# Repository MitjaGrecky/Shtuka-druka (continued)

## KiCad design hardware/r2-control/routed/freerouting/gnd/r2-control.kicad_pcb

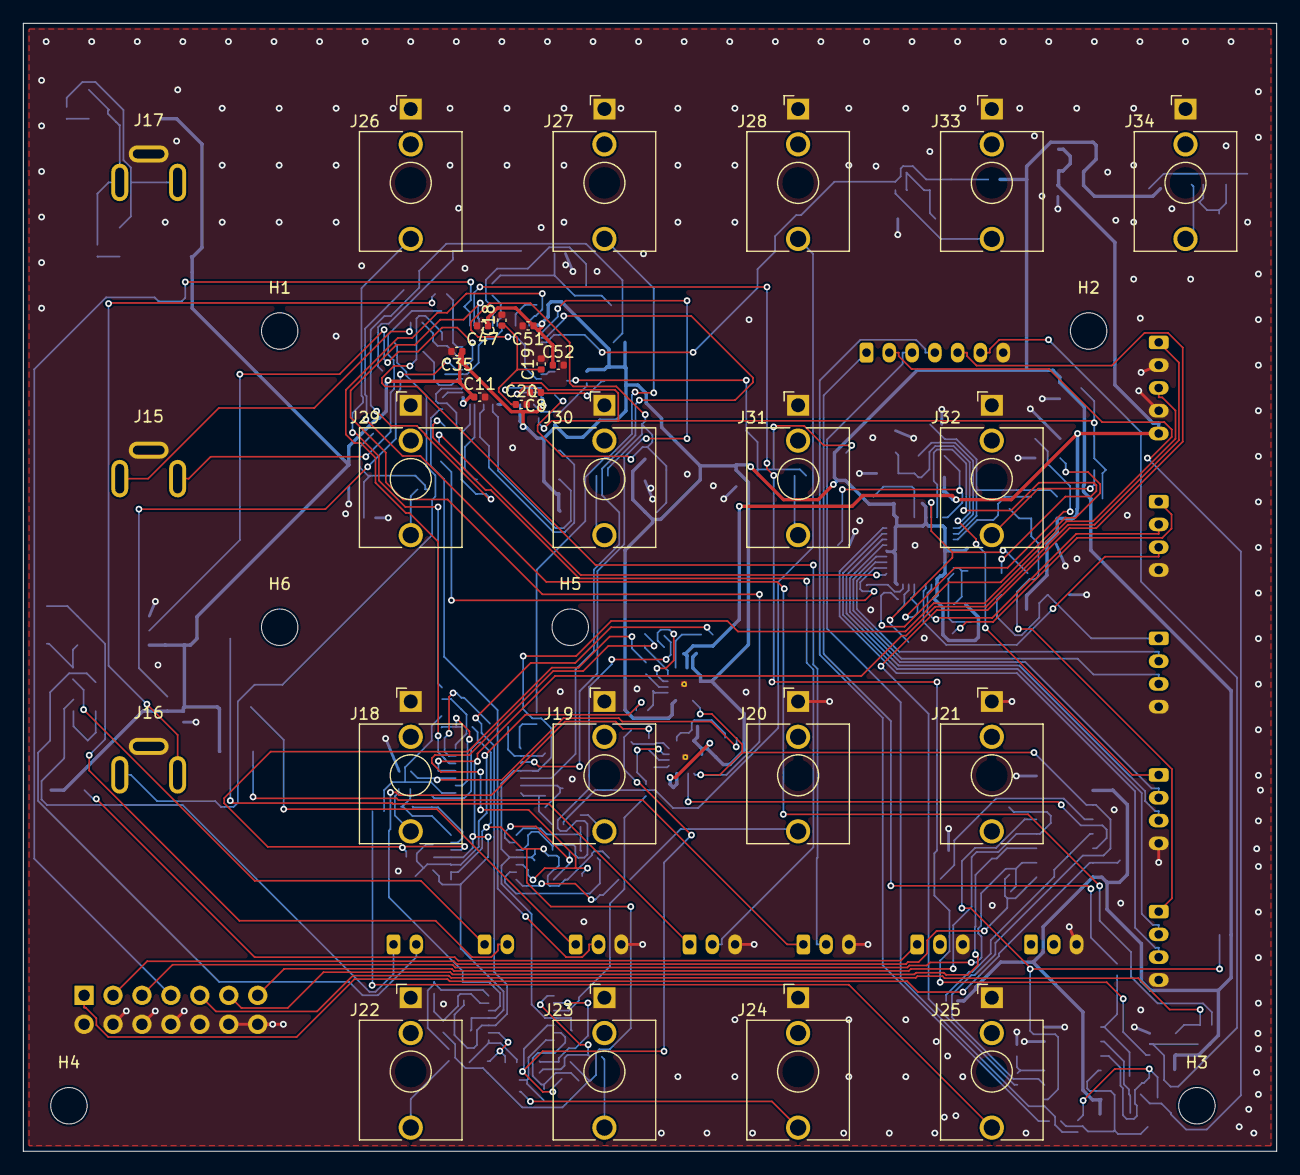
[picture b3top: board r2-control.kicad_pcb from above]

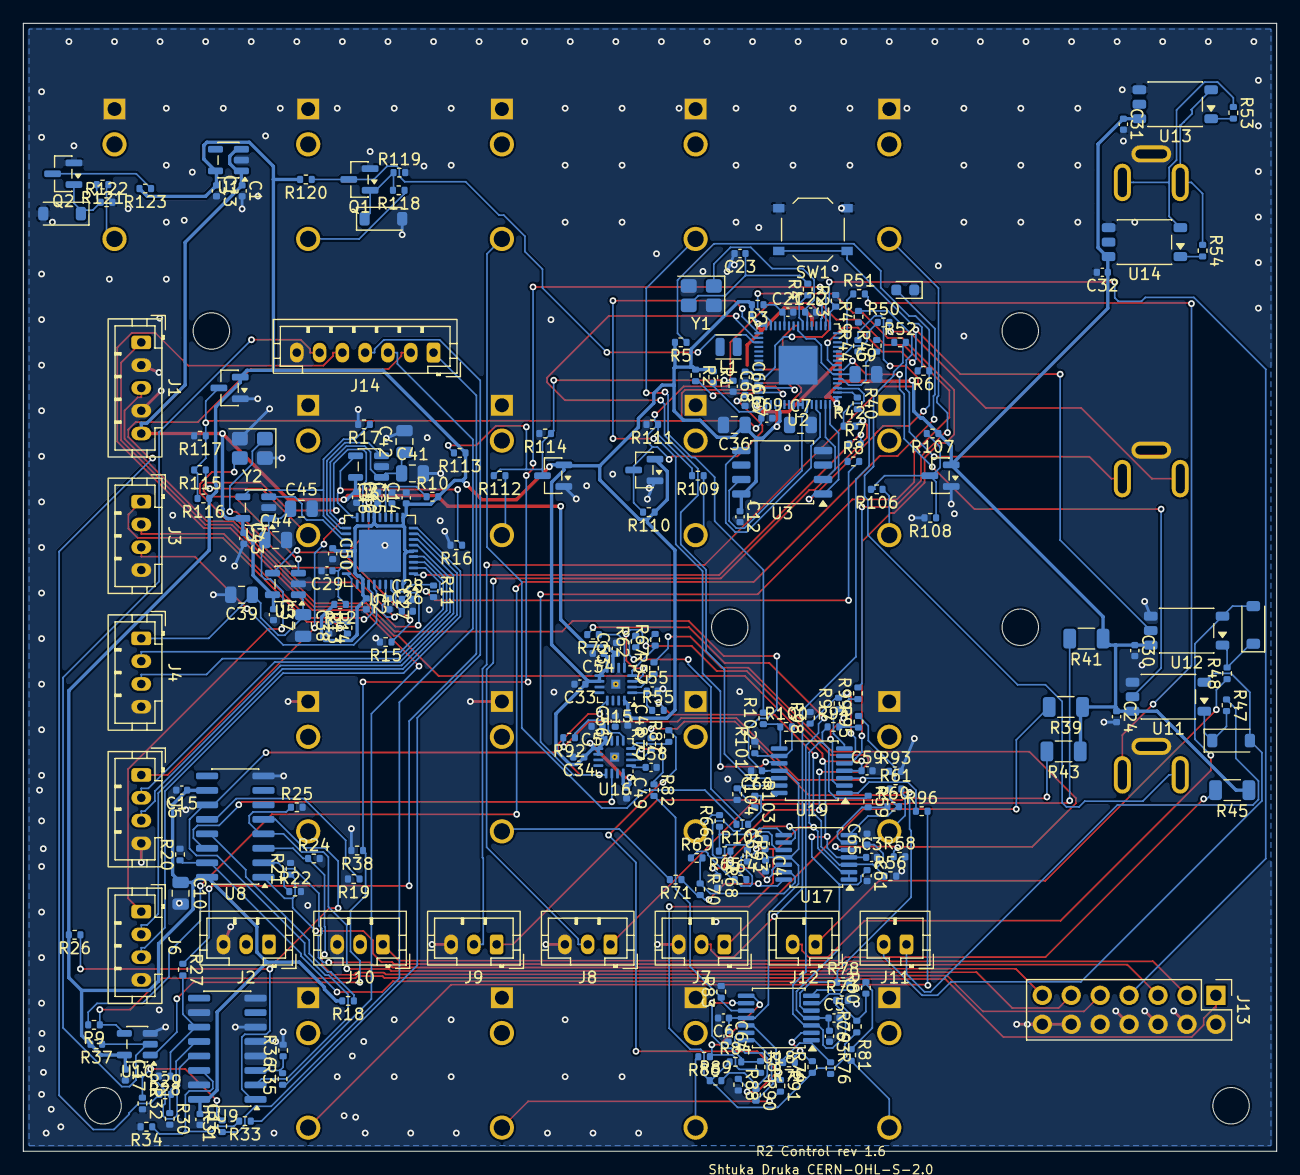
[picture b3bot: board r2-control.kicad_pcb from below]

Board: 4 copper layers, 110.0 x 99.0 mm, 266 parts (231 on the bottom side), 184 nets.

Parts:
C1, C2, C8, C29: 1u; C_0402_1005Metric
C3, C4, C5, C6, C11, C12, C13, C14, C15, C16, C17, C18, C19, C20, C21, C24, C25, C26, C30, C31, C32, C33, C34, C35, C37, C40, C43, C46, C47, C48, C49, C50, C51, C52, C53, C54, C56, C57, C59, C60, C61, C62, C63, C64, C65: 100n; C_0402_1005Metric
C7, C9, C10, C36: 4.7u; C_0805_2012Metric
C22, C23: 15p; C_0402_1005Metric
C27, C28: 18p; C_0402_1005Metric
C38, C39, C41, C42, C44, C45: 22u 10V; C_0805_2012Metric
C55, C58: 220n; C_0402_1005Metric
C66, C67, C68, C69: 10n; C_0402_1005Metric
D1: green; LED_0603_1608Metric
D2, D3, D8, D9: 1N4148W; D_SOD-123
D4, D5, D6, D7: BAT54S; SOT-23
H1, H2, H3, H4, H5, H6: M3; MountingHole_3.2mm_M3_ISO7380
J1: Power from PW; JST_PH_B5B-PH-K_1x05_P2.00mm_Vertical
J2: SWD; JST_PH_B3B-PH-K_1x03_P2.00mm_Vertical
J3: USB up; JST_PH_B4B-PH-K_1x04_P2.00mm_Vertical
J4, J5, J6: USB down; JST_PH_B4B-PH-K_1x04_P2.00mm_Vertical
J7: DIN OUT 1; JST_PH_B3B-PH-K_1x03_P2.00mm_Vertical
J8: DIN OUT 2; JST_PH_B3B-PH-K_1x03_P2.00mm_Vertical
J9: DIN OUT 3; JST_PH_B3B-PH-K_1x03_P2.00mm_Vertical
J10: DIN OUT 4; JST_PH_B3B-PH-K_1x03_P2.00mm_Vertical
J11: DIN IN 1; JST_PH_B2B-PH-K_1x02_P2.00mm_Vertical
J12: DIN IN 2; JST_PH_B2B-PH-K_1x02_P2.00mm_Vertical
J13: to A1/R1; PinHeader_2x07_P2.54mm_Vertical
J14: detect and alert; JST_PH_B7B-PH-K_1x07_P2.00mm_Vertical
J15, J16, J17: PJ-3920-3A; Jack_3.5mm_Hroparts_PJ-3920-3A_Vertical
J18, J19, J20, J21, J22, J23, J24, J25, J26, J27, J28, J29, J30, J31, J32, J33, J34: PJ398SM; Jack_3.5mm_QingPu_WQP-PJ398SM_Vertical_CircularHoles
L1: 3.3uH; L_Abracon_AOTA-B201610S
Q1, Q2: MMBT3904; SOT-23
R1, R2: 33; R_0402_1005Metric
R3, R5, R10, R12, R18, R26, R27, R29, R31, R33, R35, R37, R55, R56, R57, R59, R62, R64, R67, R69, R72, R74, R77, R79, R82, R84, R87, R89, R92, R94, R98, R101, R104, R120, R123: 10k; R_0402_1005Metric
R4, R6, R9, R61, R66, R71, R76, R81, R86, R91, R96, R99, R102, R105: 1k; R_0402_1005Metric
R7, R8: 27; R_0402_1005Metric
R11: 12k; R_0402_1005Metric
R13, R14, R15, R16, R17, R19, R20, R21, R22, R23, R24, R25, R38, R106, R109, R112, R115, R119, R122: 100k; R_0402_1005Metric
R28, R30, R32, R34, R36: 220k; R_0402_1005Metric
R39, R41, R43, R45: 33; R_1206_3216Metric
R40, R42, R44, R46: 10; R_0402_1005Metric
R47, R48, R53, R54: 220; R_0402_1005Metric
R49, R50, R51, R52: 22; R_0402_1005Metric
R58, R60, R63, R65, R68, R70, R73, R75, R78, R80, R83, R85, R88, R90, R93, R95: 80.6k; R_0402_1005Metric
R97, R100, R103: 5.1k; R_0402_1005Metric
R107, R110, R113, R116: 33k; R_0402_1005Metric
R108, R111, R114, R117: 39k; R_0402_1005Metric
R118, R121: 22k; R_0402_1005Metric
SW1: BOOTSEL; SW_Push_1P1T_XKB_TS-1187A
U1: AP2112K-3.3; SOT-23-5
U2: RP2350A; QFN-60-1EP_7x7mm_P0.4mm_EP3.4x3.4mm
U3: W25Q128JVSIQ; SOIC-8_5.3x5.3mm_P1.27mm
U4: USB2514B; QFN-36-1EP_6x6mm_P0.5mm_EP3.7x3.7mm
U5, U6, U7: TPS2051B; SOT-23-5
U8: 74HC595; SOIC-16_3.9x9.9mm_P1.27mm
U9: 74HC165; SOIC-16_3.9x9.9mm_P1.27mm
U10: 74LVC1G08; SOT-23-5
U11, U12, U13, U14: TLP2361; SO-5-6_4.55x3.7mm_P1.27mm
U15, U16: DAC80504; Texas_RTE0016D_WQFN-16-1EP_3x3mm_P0.5mm_EP0.8x0.8mm_Thermal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
U17, U18, U19: OPA4197; TSSOP-14_4.4x5mm_P0.65mm
Y1: 12MHz; Crystal_SMD_3225-4Pin_3.2x2.5mm
Y2: 24MHz; Crystal_SMD_3225-4Pin_3.2x2.5mm

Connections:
+3V3: C2.1, C10.1, C11.1, C12.1, C13.1, C14.1, C15.1, C16.1, C17.1, C24.1, C30.1, C31.1, C32.1, C33.1, C34.1, C35.1, C36.1, C46.1, C47.1, C48.1, C49.1, C50.1, C51.1, C52.1, C54.1, C57.1, D4.2, D5.2, D6.2, D7.2, R1.1, R2.1, R3.2, R5.2, R10.2, R12.2, R18.2, R26.2, R37.2, R39.1, R41.1, R43.1, R45.1, R107.1, R110.1, R113.1, R116.1, R120.2, R123.2, U1.5, U2.1, U2.11, U2.20, U2.30, U2.38, U2.45, U2.49, U2.53, U2.54, U3.8, U4.5, U4.10, U4.15, U4.23, U4.29, U4.36, U8.10, U8.16, U9.16, U10.5, U11.6, U12.6, U13.6, U14.6, U15.8, U15.9, U15.10, U15.16, U16.8, U16.9, U16.10, U16.16
+5V: C1.1, C37.1, C40.1, C43.1, C53.1, C56.1, J1.5, U1.1, U1.3, U5.5, U6.5, U7.5, U15.7, U16.7
/+12V: C3.1, C5.1, C59.1, C61.1, C63.1, J1.1, U17.4, U18.4, U19.4
/-12V: C4.1, C6.1, C60.1, C62.1, C64.1, J1.3, U17.11, U18.11, U19.11
/A1_DM: J5.2, U4.6
/A1_DP: J5.3, U4.7
/A1_OC: U4.19, U6.3
/A1_PWR: R16.1, U4.18, U6.4
/A1_VBUS: C41.1, C42.1, J5.1, U6.1
/ADC_AVDD: C8.1, R2.2, U2.44
/ATT1: J13.11, R24.1, U8.3
/ATT2: J13.13, R25.1, U8.4
/BOOTSEL: R6.2, SW1.1
/CLK_IN: Q1.3, R120.1, U2.33
/CLK_IN_B: D8.1, Q1.1, R118.2, R119.1
/CLK_IN_J: J33.T, R118.1
/CLK_OUT1: U2.29, U19.5
/CLK_OUT2: U2.31, U19.10
/CV1_J: J18.T, R61.2
/CV2_J: J19.T, R66.2
/CV3_J: J20.T, R71.2
/CV4_J: J21.T, R76.2
/CV5_J: J22.T, R81.2
/CV6_J: J23.T, R86.2
/CV7_J: J24.T, R91.2
/CV8_J: J25.T, R96.2
/CVI1_J: J29.T, R106.1
/CVI2_J: J30.T, R109.1
/CVI3_J: J31.T, R112.1
/CVI4_J: J32.T, R115.1
/CVIN1: C66.1, D4.3, R106.2, R107.2, R108.1, U2.40
/CVIN2: C67.1, D5.3, R109.2, R110.2, R111.1, U2.41
/CVIN3: C68.1, D6.3, R112.2, R113.2, R114.1, U2.42
/CVIN4: C69.1, D7.3, R115.2, R116.2, R117.1, U2.43
/CVN1: R59.2, R60.1, U17.6
/CVN2: R64.2, R65.1, U17.9
/CVN3: R69.2, R70.1, U17.13
/CVN4: R74.2, R75.1, U18.2
/CVN5: R79.2, R80.1, U18.6
/CVN6: R84.2, R85.1, U18.9
/CVN7: R89.2, R90.1, U18.13
/CVN8: R94.2, R95.1, U19.2
/CVO1: R60.2, R61.1, U17.7
/CVO2: R65.2, R66.1, U17.8
/CVO3: R70.2, R71.1, U17.14
/CVO4: R75.2, R76.1, U18.1
/CVO5: R80.2, R81.1, U18.7
/CVO6: R85.2, R86.1, U18.8
/CVO7: R90.2, R91.1, U18.14
/CVO8: R95.2, R96.1, U19.1
/CVP1: R57.2, R58.1, U17.5
/CVP2: R62.2, R63.1, U17.10
/CVP3: R67.2, R68.1, U17.12
/CVP4: R72.2, R73.1, U18.3
/CVP5: R77.2, R78.1, U18.5
/CVP6: R82.2, R83.1, U18.10
/CVP7: R87.2, R88.1, U18.12
/CVP8: R92.2, R93.1, U19.3
/DAC1: R57.1, U15.2
/DAC2: R62.1, U15.3
/DAC3: R67.1, U15.4
/DAC4: R72.1, U15.5
/DAC5: R77.1, U16.2
/DAC6: R82.1, U16.3
/DAC7: R87.1, U16.4
/DAC8: R92.1, U16.5
/DAC_CS1: U2.27, U15.12
/DAC_CS2: U2.28, U16.12
/DAC_REF1: C55.1, R55.1, U15.1
/DAC_REF2: C58.1, U16.1
/DAC_SCK: U2.18, U8.11, U9.2, U15.13, U16.13
/DAC_SDI: U2.19, U8.14, U15.14, U16.14
/DETI_AUX: R29.2, R30.1, U9.12
/DETI_HP1: R33.2, R34.1, U9.14
/DETI_HP2: R35.2, R36.1, U9.3
/DETI_MAIN: R27.2, R28.1, U9.11
/DETI_RCA: R31.2, R32.1, U9.13
/DET_AUX: J14.2, R29.1
/DET_HP1: J14.4, R33.1
/DET_HP2: J14.5, R35.1
/DET_MAIN: J14.1, R27.1
/DET_PL: R26.1, U8.5, U9.1
/DET_RCA: J14.3, R31.1
/DET_SDO: U2.37, U9.9
/DVDD: C9.1, C18.1, C19.1, C20.1, L1.2, U2.6, U2.23, U2.39, U2.50
/HUB_CRFILT: C25.1, U4.14
/HUB_OCS: R10.1, U4.13
/HUB_PLLFILT: C26.1, U4.34
/HUB_RBIAS: R11.1, U4.35
/HUB_RESET: C29.1, R12.1, U4.26
/HUB_VBUSDET: R13.2, R14.1, U4.27
/HUB_XI: C27.1, U4.33, Y2.1
/HUB_XO: C28.1, U4.32, Y2.3
/LED_K: D1.2, R9.2
/MCU_DM: R7.2, U4.1
/MCU_DM_R: R7.1, U2.51
/MCU_DP: R8.2, U4.2
/MCU_DP_R: R8.1, U2.52
/MI1_4: J11.1, R47.1
/MI1_5: D2.2, J11.2, U11.3
/MI1_A: D2.1, R47.2, U11.1
/MI2_4: J12.1, R48.1
/MI2_5: D3.2, J12.2, U12.3
/MI2_A: D3.1, R48.2, U12.1
/MIDI_RX1: U2.7, U11.5
/MIDI_RX2: U2.8, U12.5
/MIDI_TX1: R40.1, U2.2
/MIDI_TX2: R42.1, U2.3
/MIDI_TX3: R44.1, U2.4
/MIDI_TX4: R46.1, U2.5
/MO1_4: J7.1, R39.2
/MO1_5: J7.2, R40.2
/MO2_4: J8.1, R41.2
/MO2_5: J8.2, R42.2
/MO3_4: J9.1, R43.2
/MO3_5: J9.2, R44.2
/MO4_4: J10.1, R45.2
/MO4_5: J10.2, R46.2
/MUTE: J13.7, R23.1, U2.16
/P2_DM: J4.2, U4.3
/P2_DP: J4.3, U4.4
/P2_OC: U4.17, U5.3
/P2_PWR: R15.1, U4.16, U5.4
/P2_VBUS: C38.1, C39.1, J4.1, U5.1
/PH48_1: J13.1, R20.1, U8.15
/PH48_2: J13.3, R21.1, U8.1
/PHONO: J13.5, R22.1, U8.2
/PM_ALERT: J14.6, R37.1, U10.2
/QSPI_SCLK: U2.56, U3.6
/QSPI_SD0: U2.57, U3.5
/QSPI_SD1: U2.59, U3.2
/QSPI_SD2: U2.58, U3.3
/QSPI_SD3: U2.55, U3.7
/QSPI_SS: R5.1, R6.1, U2.60, U3.1
/R2_OK: J13.9, R9.1, U10.4
/R2_OK_FW: R38.1, U2.17, U10.1
/REFBUF: R59.1, R64.1, R69.1, R74.1, R79.1, R84.1, R89.1, R94.1, U17.1, U17.2
/REFHALF: C65.1, R55.2, R56.1, U17.3
/RST_IN: Q2.3, R123.1, U2.34
/RST_IN_B: D9.1, Q2.1, R121.2, R122.1
/RST_IN_J: J34.T, R121.1
/RST_OUT: U2.32, U19.12
/RUN: C21.1, R3.1, U2.26
/SO1_J: J26.T, R99.2
/SO1_N: R97.2, R98.1, U19.6
/SO1_O: R97.1, R99.1, U19.7
/SO2_J: J27.T, R102.2
/SO2_N: R100.2, R101.1, U19.9
/SO2_O: R100.1, R102.1, U19.8
/SO3_J: J28.T, R105.2
/SO3_N: R103.2, R104.1, U19.13
/SO3_O: R103.1, R105.1, U19.14
/SP_DM: J6.2, U4.8
/SP_DP: J6.3, U4.9
/SP_OC: U4.21, U7.3
/SP_PWR: R17.1, U4.20, U7.4
/SP_VBUS: C44.1, C45.1, J6.1, U7.1
/SWCLK: J2.1, U2.24
/SWDIO: J2.2, U2.25
/TIA_A: R53.2, U13.1
/TIB_A: R54.2, U14.1
/TI_R: J17.R, R54.1, U13.3
/TI_T: J17.T, R53.1, U14.3
/TO1_R: J15.R, R50.2
/TO1_T: J15.T, R49.2
/TO2_R: J16.R, R52.2
/TO2_T: J16.T, R51.2
/TRS1_R: R50.1, U2.10
/TRS1_T: R49.1, U2.9
/TRS2_R: R52.1, U2.13
/TRS2_T: R51.1, U2.12
/TRSIN_A: U2.14, U13.5
/TRSIN_B: U2.15, U14.5
/UP_DM: J3.2, U4.30
/UP_DP: J3.3, U4.31
/UP_VBUS: J3.1, R13.1
/VREG_AVDD: C7.1, R1.2, U2.46
/VREG_LX: L1.1, U2.48
/XIN: C22.1, U2.21, Y1.1
/XOUT: R4.1, U2.22
/XR_LATCH: R19.1, U2.35, U8.12
/XR_OE: R18.1, U2.36, U8.13
/XTAL_O: C23.1, R4.2, Y1.3
GND: C1.2, C2.2, C3.2, C4.2, C5.2, C6.2, C7.2, C8.2, C9.2, C10.2, C11.2, C12.2, C13.2, C14.2, C15.2, C16.2, C17.2, C18.2, C19.2, C20.2, C21.2, C22.2, C23.2, C24.2, C25.2, C26.2, C27.2, C28.2, C29.2, C30.2, C31.2, C32.2, C33.2, C34.2, C35.2, C36.2, C37.2, C38.2, C39.2, C40.2, C41.2, C42.2, C43.2, C44.2, C45.2, C46.2, C47.2, C48.2, C49.2, C50.2, C51.2, C52.2, C53.2, C54.2, C55.2, C56.2, C57.2, C58.2, C59.2, C60.2, C61.2, C62.2, C63.2, C64.2, C65.2, C66.2, C67.2, C68.2, C69.2, D1.1, D4.1, D5.1, D6.1, D7.1, D8.2, D9.2, J1.2, J1.4, J2.3, J3.4, J4.4, J5.4, J6.4, J7.3, J8.3, J9.3, J10.3, J13.2, J13.4, J13.6, J13.8, J13.10, J13.12, J13.14, J14.7, J15.S, J16.S, J17.S, J18.S, J19.S, J20.S, J21.S, J22.S, J23.S, J24.S, J25.S, J26.S, J27.S, J28.S, J29.S, J30.S, J31.S, J32.S, J33.S, J34.S, Q1.2, Q2.2, R11.2, R14.2, R15.2, R16.2, R17.2, R19.2, R20.2, R21.2, R22.2, R23.2, R24.2, R25.2, R28.2, R30.2, R32.2, R34.2, R36.2, R38.2, R56.2, R58.2, R63.2, R68.2, R73.2, R78.2, R83.2, R88.2, R93.2, R98.2, R101.2, R104.2, R108.2, R111.2, R114.2, R117.2, R119.2, R122.2, SW1.2, U1.2, U2.47, U2.61, U3.4, U4.11, U4.37, U5.2, U6.2, U7.2, U8.8, U9.4, U9.5, U9.6, U9.8, U9.10, U9.15, U10.3, U11.4, U12.4, U13.4, U14.4, U15.6, U15.11, U15.17, U16.6, U16.11, U16.17, Y1.2, Y1.4, Y2.2, Y2.4

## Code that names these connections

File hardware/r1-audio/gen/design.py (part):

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        CP("47u 25V", "+12V", fp=CP63)
        CP("47u 25V", "GND", "-12V", fp=CP63)
    add(ref("J"), "Connector_Generic:Conn_02x07_Odd_Even", "from R2", "Connector_PinHeader_2.54mm:PinHeader_2x07_P2.54mm_Vertical",
        {"1": "PH48_1", "2": "GND", "3": "PH48_2", "4": "GND", "5": "PHONO", "6": "GND", "7": "MUTE", "8": "GND", "9": "R2_OK",
         "10": "GND", "11": "ATT1", "12": "GND", "13": "ATT2", "14": "GND"},
        Note="same pinout as R2 'to A1/R1' (2x7 from rev 0.3: ATT1/ATT2 = Mic/Line attenuator relays); all lines pulled low on R2 while it boots")

    add(ref("J"), "Connector_Generic:Conn_01x05", "to F1 (mute, detect)", "Connector_JST:JST_PH_B5B-PH-K_1x05_P2.00mm_Vertical",
        {"1": "MUTE", "2": "R2_OK", "3": "GND", "4": "DET_HP1", "5": "DET_HP2"}, Note="P154 (rev 1.4): 5 pins = F1 J3 (pins 4, 5 cable detect HP1/HP2, passed to R2 by the next header). MUTE and R2_OK for the headphone relays on F1 (parallel to the output relay logic); "
        "the headphone board is at the front edge, R2's connector to R1 stays 2x7")
    add(ref("J"), "Connector_Generic:Conn_01x03", "HP detect to R2", "Connector_JST:JST_PH_B3B-PH-K_1x03_P2.00mm_Vertical",
        {"1": "DET_HP1", "2": "DET_HP2", "3": "GND"}, Note="P154: headphone cable detect from F1 to the R2 7-pin detect header (pins 4, 5, 7); one harness housing on R2 collects R1, F1 and PW PM_ALERT wires")

    # ---------------------------------------------------------------- board-to-board to A1
    adc = [f"ADC{k}" for k in range(1, 19)]
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        Note="harness H9: Johnson 111-0702-001 binding post (ring or fork lug, 6-32), 20 AWG, 12 cm; both pins GND (two wires to one lug); the post is a bonding point, the panel contact decides chassis vs signal ground (doc 49)")
    add(ref("J"), "Connector_Generic:Conn_01x03", "Phono/Line switch", "Connector_JST:JST_PH_B3B-PH-K_1x03_P2.00mm_Vertical",
        {"1": "+5V", "2": "SW_PHONO", "3": "GND"},
        Note="harness H10: NKK M2012S2A1W01 SPDT ON-ON, 26-28 AWG x 3: pin 1 = common (+5V), pin 2 = Phono throw (forces the phono relays, OR with R2), pin 3 = Line throw (GND: no force; R2 controls)")
    K.mount_holes(add, ref, HOLES, "M3 standoff (Codex review 15.11.2026): corners first; the final positions come with the enclosure")
    return P

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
